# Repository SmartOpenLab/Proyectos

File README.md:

# Proyectos
Project's Repository of [Smart Open Lab](http://www.smartopenlab.com)

- Insoladora - Two faces PCB insolator device using UV light
- IoT_WeightMeasure - Weight measure device based on ESP8266
- Cerradura Biométrica - IoT door lock device based on fingerprints
- ESP rfid keypad access - Clone of [esp-rfid](https://github.com/esprfid/esp-rfid) 
- esp_rfid_SOL_V1 - IoT door lock device based on ESP8266 with RFID reader and keyboard. With custom PCB with MOSFET instead of relay.
- OpenSoundMeter - IoT sound preassure meter device.

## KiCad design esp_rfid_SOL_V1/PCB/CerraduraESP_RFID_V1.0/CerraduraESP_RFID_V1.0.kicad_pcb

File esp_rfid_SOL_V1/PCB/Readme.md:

Kicad files for the schematic and PCB.

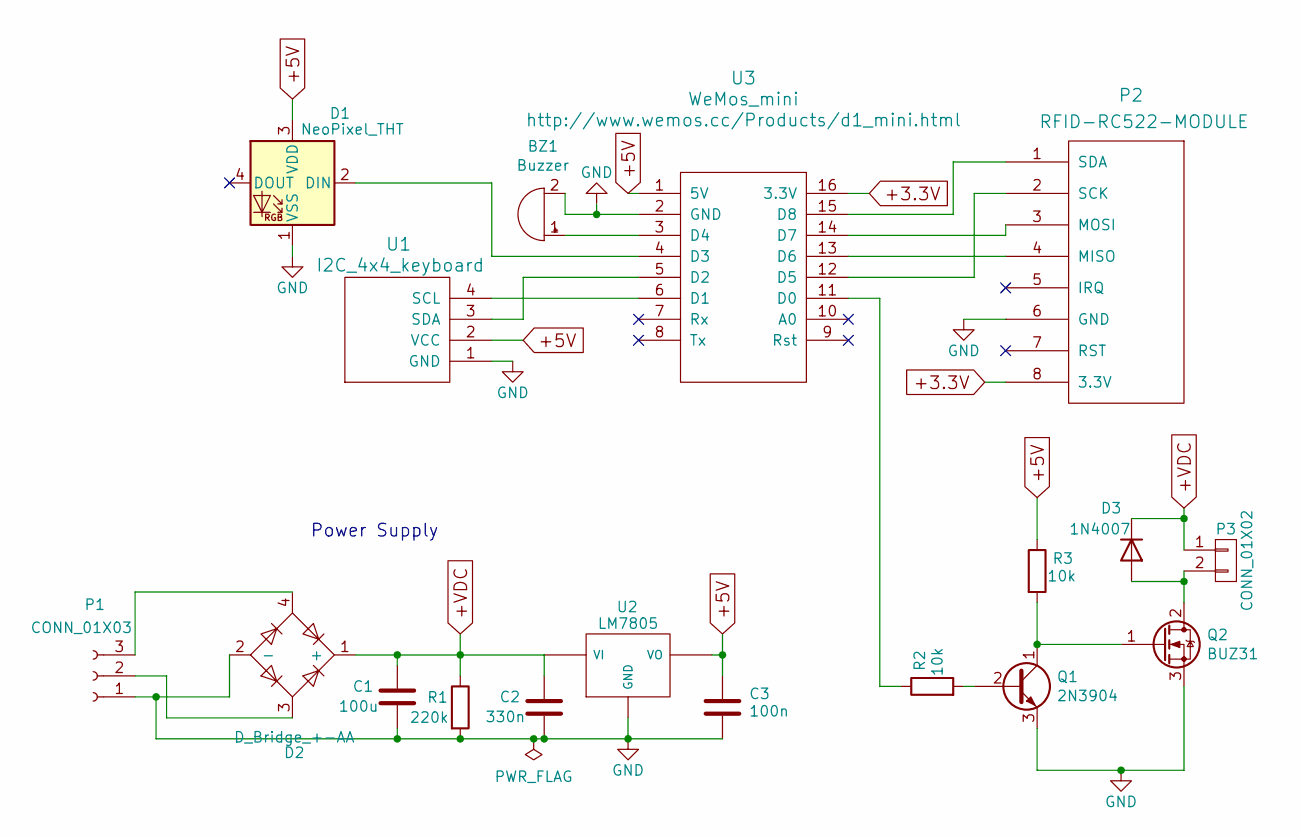
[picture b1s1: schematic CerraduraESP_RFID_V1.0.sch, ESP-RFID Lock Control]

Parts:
BZ1: Buzzer; Buzzer_12x9.5RM7.6
C1: 100u; CP_Radial_D10.0mm_P3.80mm
C2: 330n; C_Disc_D5.0mm_W2.5mm_P2.50mm
C3: 100n; C_Rect_L7.0mm_W2.5mm_P5.00mm
D1: NeoPixel_THT; Socket_Strip_Straight_1x03_Pitch2.54mm
D2: D_Bridge_+-AA; Diode_Bridge_Round_D8.9mm
D3: 1N4007; D_DO-41_SOD81_P7.62mm_Horizontal
P1: CONN_01X03; TerminalBlock_bornier-3_P5.08mm
P2: RFID-RC522-MODULE; Socket_Strip_Straight_1x08_Pitch2.54mm
P3: CONN_01X02; TerminalBlock_bornier-2_P5.08mm
Q1: 2N3904; TO-92_Inline_Wide
Q2: BUZ31; TO-220-3_Vertical
R1: 220k; R_Axial_DIN0207_L6.3mm_D2.5mm_P7.62mm_Horizontal
R2, R3: 10k; R_Axial_DIN0207_L6.3mm_D2.5mm_P7.62mm_Horizontal
U1: I2C_4x4_keyboard; Socket_Strip_Straight_1x04_Pitch2.54mm
U2: LM7805; TO-220-3_Vertical
U3: WeMos_mini; wemos-d1-mini-with-pin-header-and-connector

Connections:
+3.3V: P2.8 (3.3V), U3.16 (3.3V)
+5V: C3.1, D1.3 (VDD), R3.1, U1.2 (VCC), U2.3 (VO), U3.1 (5V)
+VDC: C1.1, C2.1, D2.1 (+), D3.1 (K), P3.1, R1.1, U2.1 (VI)
GND: BZ1.2 (+), C1.2, C2.2, C3.2, D1.1 (VSS), D2.2 (-), P1.1, P2.6 (GND), Q1.3 (E), Q2.3 (S), R1.2, U1.1 (GND), U2.2 (GND), U3.2 (GND)
unnamed: BZ1.1 (-), U3.3 (D4)
unnamed: D1.2 (DIN), U3.4 (D3)
unnamed: D2.3, P1.2
unnamed: D2.4, P1.3
unnamed: D3.2 (A), P3.2, Q2.2 (D)
unnamed: P2.1 (SDA), U3.15 (D8)
unnamed: P2.2 (SCK), U3.12 (D5)
unnamed: P2.3 (MOSI), U3.14 (D7)
unnamed: P2.4 (MISO), U3.13 (D6)
unnamed: Q1.1 (C), Q2.1 (G), R3.2
unnamed: Q1.2 (B), R2.2
unnamed: R2.1, U3.11 (D0)
unnamed: U1.3 (SDA), U3.5 (D2)
unnamed: U1.4 (SCL), U3.6 (D1)

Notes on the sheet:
Power Supply

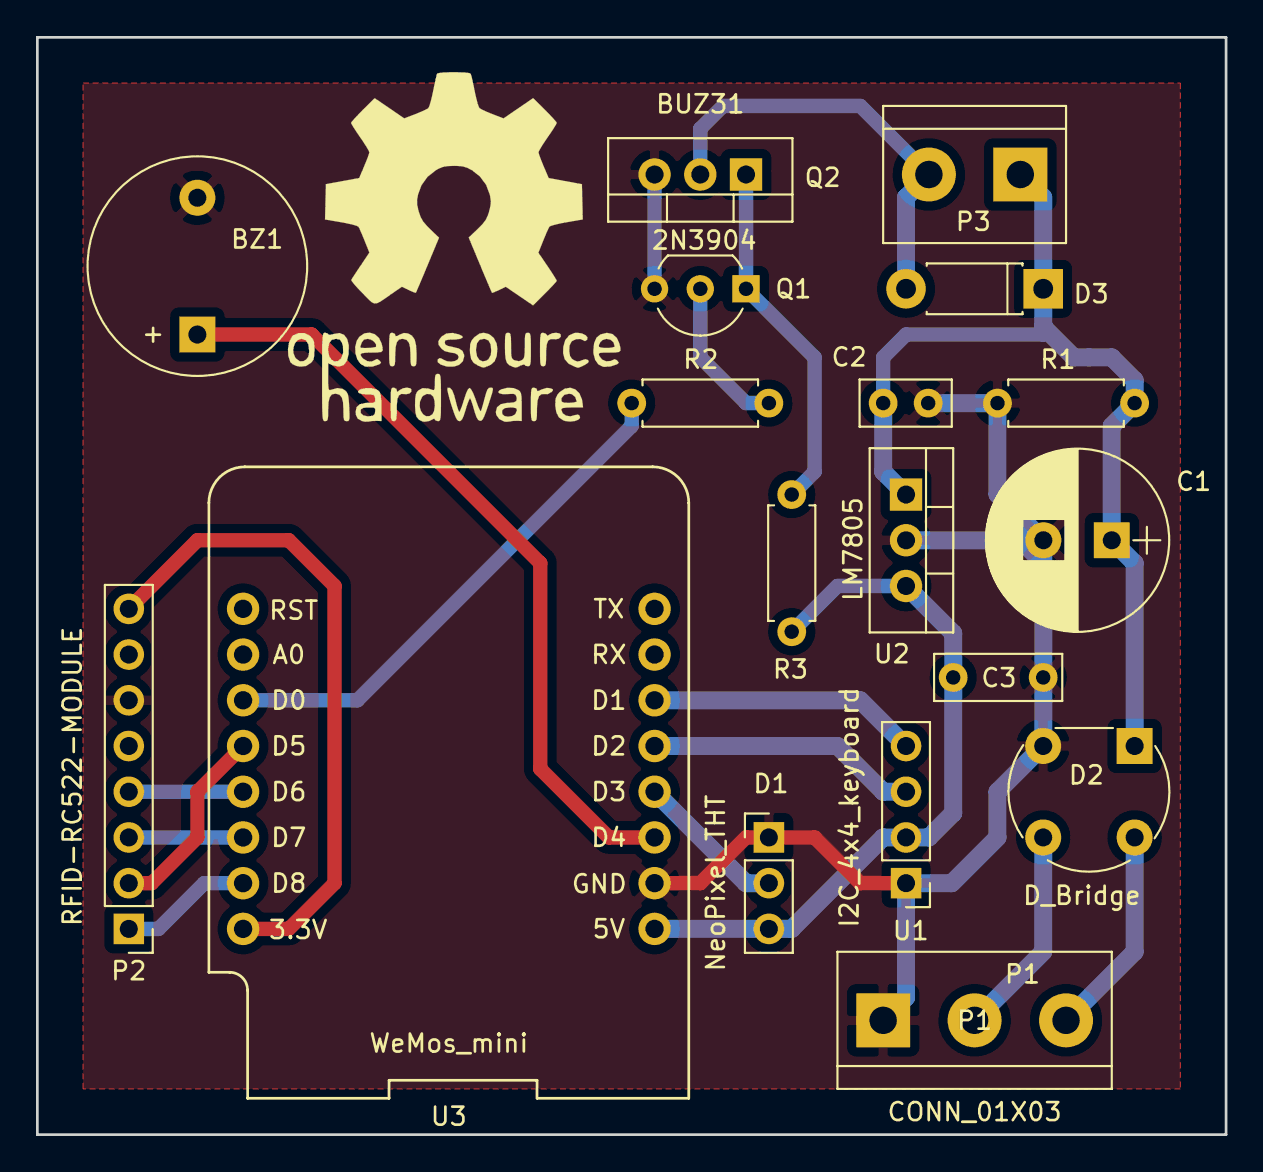
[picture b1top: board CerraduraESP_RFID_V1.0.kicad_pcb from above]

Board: 2 copper layers, 66.0 x 61.0 mm, 18 parts (0 on the bottom side), 18 nets.

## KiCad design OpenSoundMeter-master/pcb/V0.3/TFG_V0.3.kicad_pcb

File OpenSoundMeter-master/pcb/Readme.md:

# Electronic Design

We developed a PCB for preamplification, filtering and integration of the analog input signal.

### Prerequisites

Kicad 4.0 or later.

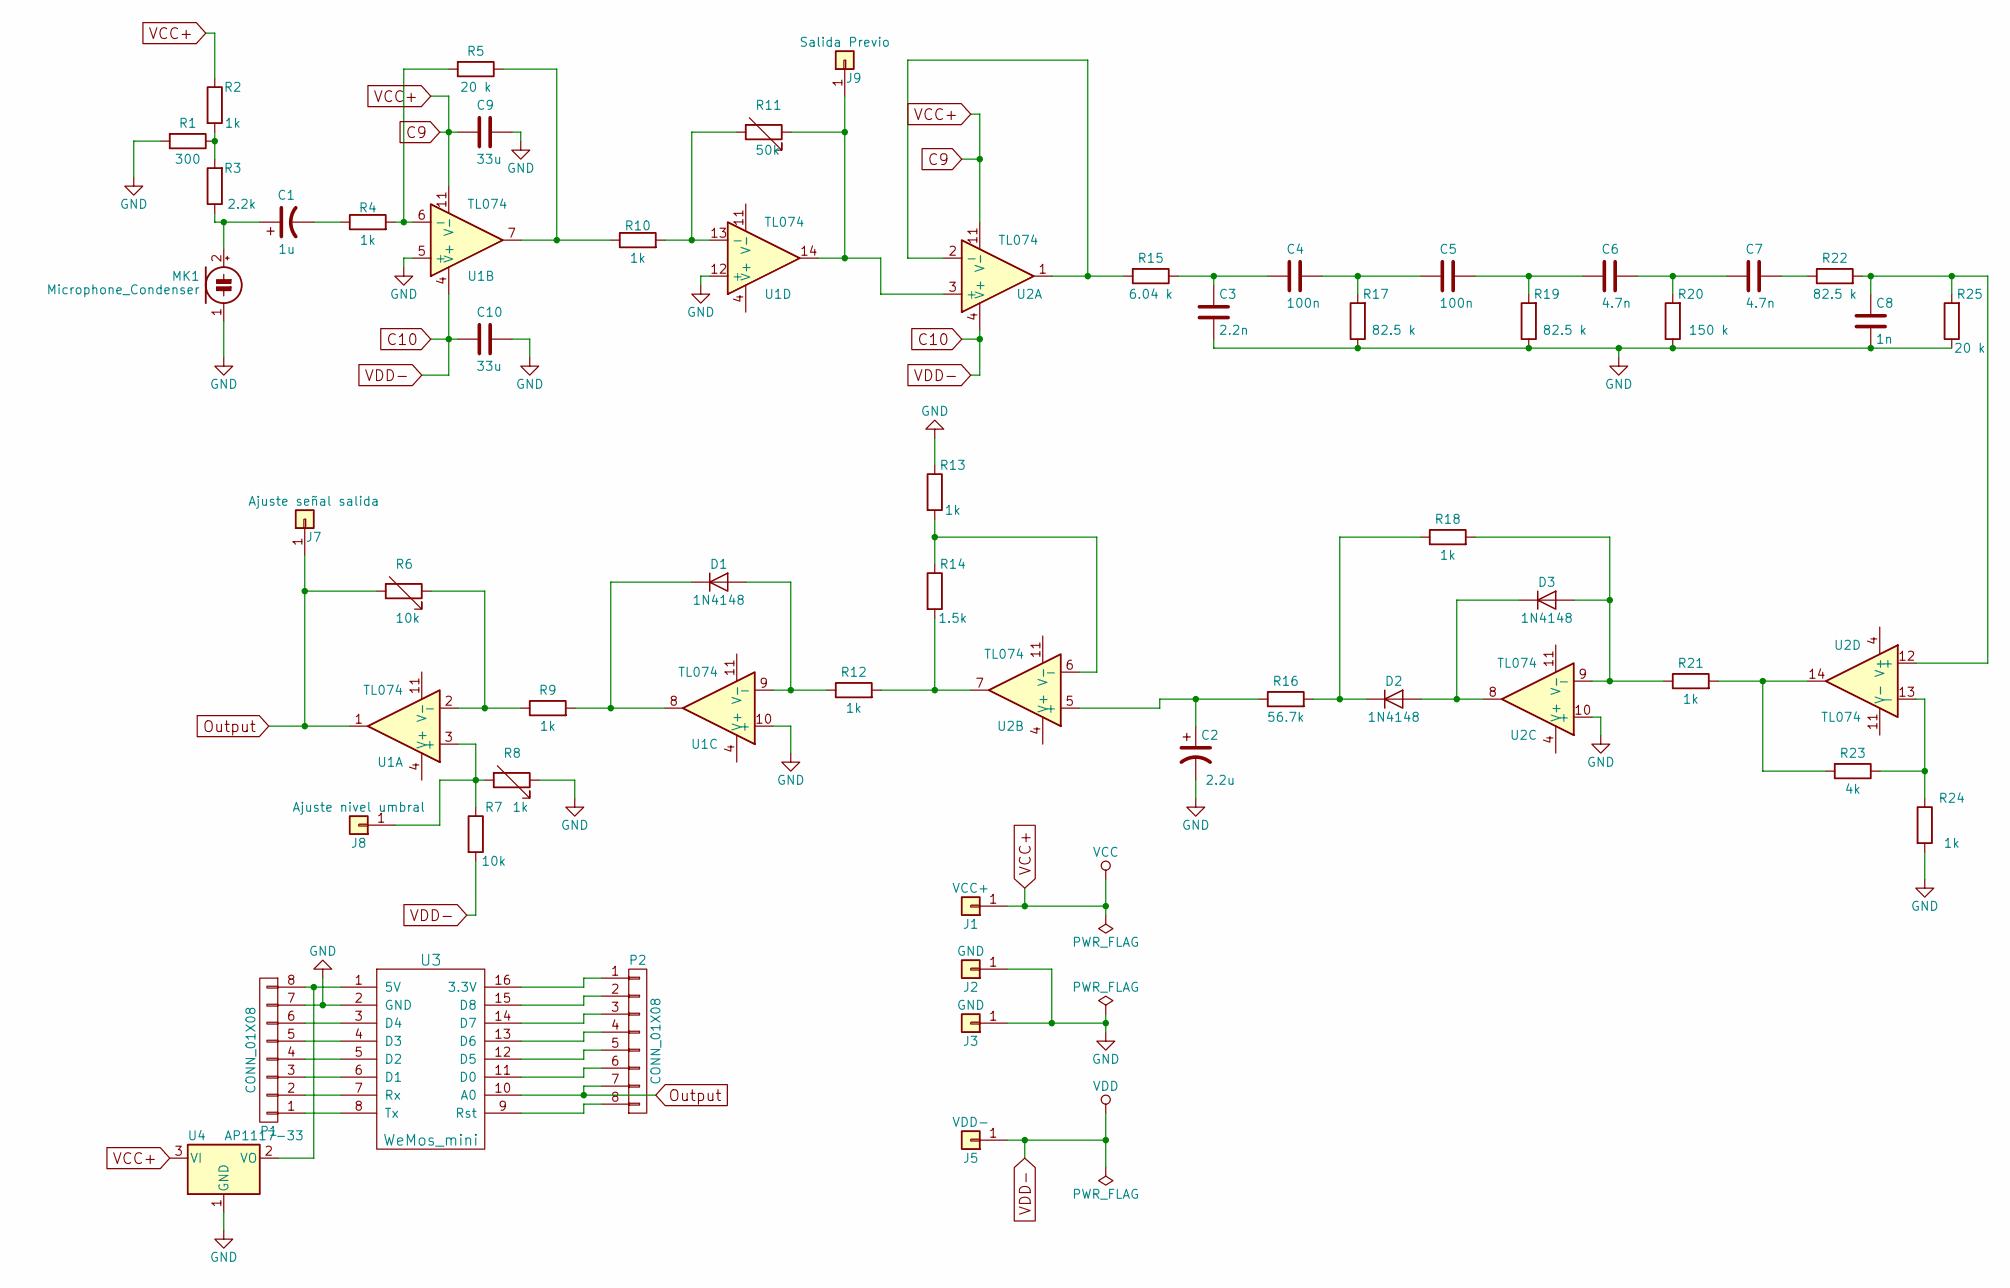
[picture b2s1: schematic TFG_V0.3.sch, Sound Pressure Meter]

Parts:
C1: 1u; C_Axial_L3.8mm_D2.6mm_P10.00mm_Horizontal
C2: 2.2u; C_Axial_L3.8mm_D2.6mm_P10.00mm_Horizontal
C3: 2.2n; C_Disc_D4.3mm_W1.9mm_P5.00mm
C4, C5: 100n; C_Rect_L7.0mm_W2.0mm_P5.00mm
C6, C7: 4.7n; C_Disc_D4.3mm_W1.9mm_P5.00mm
C8: 1n; C_Disc_D4.3mm_W1.9mm_P5.00mm
C9, C10: 33u; C_Axial_L3.8mm_D2.6mm_P10.00mm_Horizontal
D1, D2, D3: 1N4148; D_T-1_P5.08mm_Horizontal
J1: VCC+; Pin_Header_Angled_1x01_Pitch1.27mm
J2, J3: GND; Pin_Header_Angled_1x01_Pitch1.27mm
J5: VDD-; Pin_Header_Angled_1x01_Pitch1.27mm
J7: Ajuste señal salida; Pin_Header_Angled_1x01_Pitch1.27mm
J8: Ajuste nivel umbral; Pin_Header_Angled_1x01_Pitch1.27mm
J9: Salida Previo; Pin_Header_Angled_1x01_Pitch1.27mm
MK1: Microphone_Condenser; WireConnection_0.80mmDrill
P1, P2: CONN_01X08; Pin_Header_Straight_1x08_Pitch1.00mm
R1: 300; R_Axial_DIN0204_L3.6mm_D1.6mm_P7.62mm_Horizontal
R2, R4, R9, R10, R12, R13, R18, R21, R24: 1k; R_Axial_DIN0204_L3.6mm_D1.6mm_P7.62mm_Horizontal
R3: 2.2k; R_Axial_DIN0204_L3.6mm_D1.6mm_P7.62mm_Horizontal
R5, R25: 20 k; R_Axial_DIN0204_L3.6mm_D1.6mm_P7.62mm_Horizontal
R6: 10k; Potentiometer_Trimmer_Bourns_3296Y
R7: 10k; R_Axial_DIN0204_L3.6mm_D1.6mm_P7.62mm_Horizontal
R8: 1k; Potentiometer_Trimmer_Bourns_3296Y
R11: 50k; Potentiometer_Trimmer_Bourns_3296Y
R14: 1.5k; R_Axial_DIN0204_L3.6mm_D1.6mm_P7.62mm_Horizontal
R15: 6.04 k; R_Axial_DIN0204_L3.6mm_D1.6mm_P7.62mm_Horizontal
R16: 56.7k; R_Axial_DIN0204_L3.6mm_D1.6mm_P7.62mm_Horizontal
R17, R19, R22: 82.5 k; R_Axial_DIN0204_L3.6mm_D1.6mm_P7.62mm_Horizontal
R20: 150 k; R_Axial_DIN0204_L3.6mm_D1.6mm_P7.62mm_Horizontal
R23: 4k; R_Axial_DIN0204_L3.6mm_D1.6mm_P7.62mm_Horizontal
U1, U2: TL074; DIP-14_W7.62mm
U3: WeMos_mini; D1_mini_board
U4: AP1117-33; TO-220-3_Vertical

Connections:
C9: C9.2, J1.1, R2.1, U1.11 (V-), U2.11 (V-), U4.3 (VI)
C10: C10.2, J5.1, R7.2, U1.4 (V+), U2.4 (V+)
GND: C2.2, C3.2, C8.2, C9.1, C10.1, J2.1, J3.1, MK1.1 (-), P1.7, R1.2, R8.1, R13.1, R17.1, R19.1, R20.1, R24.2, R25.1, U1.5 (+), U1.10 (+), U1.12 (+), U2.10 (+), U3.2 (GND), U4.1 (GND)
unnamed: C1.1, MK1.2 (+), R3.1
unnamed: C1.2, R4.1
unnamed: C2.1, R16.1, U2.5 (+)
unnamed: C3.1, C4.2, R15.1
unnamed: C4.1, C5.2, R17.2
unnamed: C5.1, C6.2, R19.2
unnamed: C6.1, C7.2, R20.2
unnamed: C7.1, R22.1
unnamed: C8.1, R22.2, R25.2, U2.12 (+)
unnamed: D1.1 (K), R9.2, U1.8
unnamed: D1.2 (A), R12.1, U1.9 (-)
unnamed: D2.1 (K), R16.2, R18.1
unnamed: D2.2 (A), D3.1 (K), U2.8
unnamed: D3.2 (A), R18.2, R21.1, U2.9 (-)
unnamed: J8.1, R7.1, R8.2, U1.3 (+)
unnamed: J9.1, R11.1, U1.14, U2.3 (+)
unnamed: P1.1, U3.8 (Tx)
unnamed: P1.2, U3.7 (Rx)
unnamed: P1.3, U3.6 (D1)
unnamed: P1.4, U3.5 (D2)
unnamed: P1.5, U3.4 (D3)
unnamed: P1.6, U3.3 (D4)
unnamed: P1.8, U3.1 (5V), U4.2 (VO)
unnamed: P2.1, U3.16 (3.3V)
unnamed: P2.2, U3.15 (D8)
unnamed: P2.3, U3.14 (D7)
unnamed: P2.4, U3.13 (D6)
unnamed: P2.5, U3.12 (D5)
unnamed: P2.6, U3.11 (D0)
unnamed: P2.8, U3.9 (Rst)
unnamed: R1.1, R2.2, R3.2
unnamed: R4.2, R5.2, U1.6 (-)
unnamed: R6.1, R9.1, U1.2 (-)
unnamed: R5.1, R10.1, U1.7
unnamed: R10.2, R11.2, U1.13 (-)
unnamed: R12.2, R14.2, U2.7
unnamed: R13.2, R14.1, U2.6 (-)
unnamed: R15.2, U2.1, U2.2 (-)
unnamed: R21.2, R23.2, U2.14
unnamed: R23.1, R24.1, U2.13 (-)
Output: J7.1, P2.7, R6.2, U1.1, U3.10 (A0)

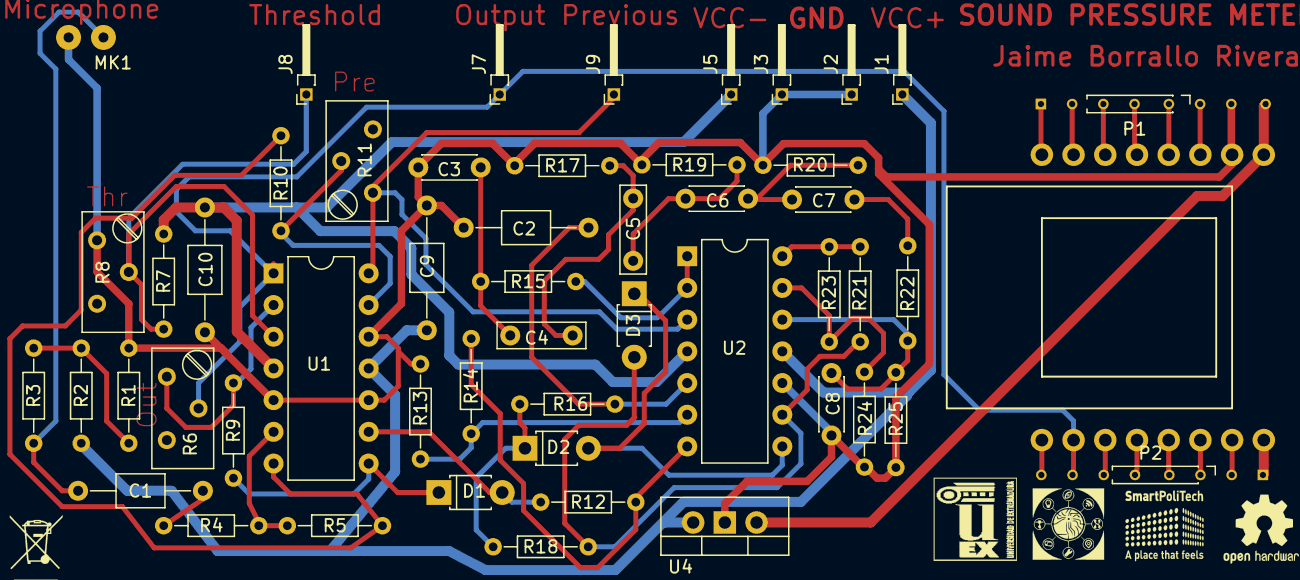
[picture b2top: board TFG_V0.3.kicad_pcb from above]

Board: 2 copper layers, 52 parts (1 on the bottom side), 44 nets.

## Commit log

2017-04-10 Añadido repositorio ejemploGit
2017-11-28 Añadido proyecto insoladora by @David867.
2017-11-28 Añadido el proyecto IoT_Balanza by @AGordiGuerrero.
2018-04-10 Añadido proyecto Cerradura Biométrica by @joriks
    Repositorio original: https://github.com/Joriks/Biometric-lock
2018-04-10 Actualizado readme con los proyectos
2019-01-11 Added a fork from esp-rfid v1.0.0
2019-01-11 Added password on website and save process for access
2019-01-20 Added empty value to default on new user
2019-01-27 Removed update by esp-rfid repository
2019-01-27 Removed neo bypass of admin settings
2019-10-21 Bump mixin-deep in /esp-rfid-keypad-access/tools/webfilesbuilder
    Bumps [mixin-deep](https://github.com/jonschlinkert/mixin-deep) from 1.3.1 to 1.3.2.
    - [Release notes](https://github.com/jonschlinkert/mixin-deep/releases)
    - [Commits](https://github.com/jonschlinkert/mixin-deep/compare/1.3.1...1.3.2)
2020-12-03 Added LICENSE BY-NC-SA
2020-12-03 Delete user from system
    Fully feature of manual deleting user from system
2020-12-03 Fixed minor bug on Unsubscribe print
    Deleted the view of the identifier and fixed unsubscribe help print
2020-12-03 Fixed bug end bracket of subscribe module
2020-12-03 Fixed bugs with Fingerprints uses
    Unsuscribe module did not erase finger_id correct.
    Check fingerprint module
    -Wait was skipped after the first pause
    -Infinite loop because of no check of state of fingerprint
    Check finger image infinite loop because of no check of state of fingerprint.
    Getter fingerprint changed delay to showLed module and added some Debug notes
2020-12-03 Added OLED Support
    Added OLED support with a 128x64px OLED and u8glib.
    Added draw module for print messages on OLED Screen
2020-12-03 Add new user to system
    Fully feature of adding new users to system
2020-12-03 Skeleton to using KeypadEvents
    Refactor of first code implementation (add and check fingerprints)
    added structure control defined on use cases
2020-12-03 Check Admin Fingerprints
    Checking fingerprints to control Admin recourses
2020-12-03 Added module to include new control fingerprint
    Control module with subscribe control fingerprint option implemented.
2020-12-03 Checking fingerprints, main case of biometric locker
    Check of any type of fingerprint returns fingerID if it exsits on system
2020-12-03 Added Compilation directive and Led Information
    Added Debug compilation directive to use it with screen prints and show information by Serial.
    Added a led module to show information with red, green and white leds for errors, pass and activity information
2020-12-03 Añadido fichero base de la cerradura biométrica
    Fichero con la base operativa de la cerradura biométrica
2020-12-03 Fixed bugs in subscribe & getting password
    Changed Keyboard input from Event Listener to Wait for key, locker method.
    Migrated code from Event Listener to main loop.
    Added to main loop getting password to store on system, because it fails because of nesting.
    Split getPassword module to check on one side an get on the other (getKeyPass module).
    Minor changes in variable names
2020-12-03 Obtain Fingerprint Model
    Obtain a fingerprint twice and genereate a model, with time chunk
2020-12-03 Added check password for subscribe module
    Added a checker password, with two comprobations to add new user into the system
2020-12-03 Added Check Access & changed relay & fingerprint pinout
    Added checkAccess module to check fingerprints and allow or deny access.
    Changed Relay pinout from Digital 10 to Analog 3
    Changed Fingerprint Sensor pinout from 11,12 to 10,11
2020-12-03 Changed all information messages from english to spanish
2020-12-03 Changed sensor pinout, deleted event keypad, deleted password nesting
    Changed sensor pinout from 11,12 to 10,11.
    Deleted Event listener from keypad, and added control to main loop.
    Deleted password nesting on getPassword to show information messages.
2020-12-03 Changed text of information messages
2020-12-03 Refactor of secundary modules
    Refactor and optimization of secundary modules
    Renamed modules with more understandable names
2020-12-03 Added Reset function by master keys
2020-12-03 Added Reset function by fingerprint
    Created factory Reset function to delete all and restore default settings
2020-12-03 Refactor of unsubscribe user
    optimization of unsubscribe user module using refactorized secundary modules
2020-12-03 Ccorreciones
2020-12-03 Added Unsubscribe control user function
2020-12-03 Correciones
2020-12-03 Added persistence feature
    Added persistence using EEPROM to save passwords and state of the system
2020-12-03 Revert "Added id info message on subscribe & info message on unsubscribe module"
    This reverts commit 1e845f3bf3ee7c0138c4196bffbc737122458188.
2020-12-03 Added id info message on subscribe & info message on unsubscribe module
    Added information message with id of the actual user adder to system.
    Added information message on unsubscribe module asking for a fingerprint.
2020-12-03 Added check of id data & Information on control checks
    Added check of integrity user & control id
    Added information error on check password of control module
2020-12-03 Changed condition to isdigit() & added compilation primitives
    Changed condition of check keycode to isdigit() from ascii decimal values
    Added compilation primitives to select LED, OLED or both modes
2020-12-03 Changed actuator opening time
    Changed to 100 ms to use dc and control status of actuator
2020-12-03 Adjust of all information messages printed on OLED
2020-12-03 Migrated Serial library uses to DEBUG MODE
2020-12-03 Fixed Display of user information over Serial and OLED
    Temporal fixed to display user id over OLED
2020-12-03 Merged from remote repo
2020-12-11 Bump ini in /esp-rfid-keypad-access/tools/webfilesbuilder
    Bumps [ini](https://github.com/isaacs/ini) from 1.3.5 to 1.3.7.
    - [Release notes](https://github.com/isaacs/ini/releases)
    - [Commits](https://github.com/isaacs/ini/compare/v1.3.5...v1.3.7)
2021-08-10 Bump path-parse in /esp-rfid-keypad-access/tools/webfilesbuilder
    Bumps [path-parse](https://github.com/jbgutierrez/path-parse) from 1.0.6 to 1.0.7.
    - [Release notes](https://github.com/jbgutierrez/path-parse/releases)
    - [Commits](https://github.com/jbgutierrez/path-parse/commits/v1.0.7)
    ---
    updated-dependencies:
    - dependency-name: path-parse
2021-12-08 Create ESP-RFID-KEYBOARD_SOL_V1
2022-11-01 Bump minimatch and gulp in /esp-rfid-keypad-access/tools/webfilesbuilder
    Bumps [minimatch](https://github.com/isaacs/minimatch) to 3.1.2 and updates ancestor dependency [gulp](https://github.com/gulpjs/gulp). These dependencies need to be updated together.
    Updates `minimatch` from 0.2.14 to 3.1.2
    - [Release notes](https://github.com/isaacs/minimatch/releases)
    - [Commits](https://github.com/isaacs/minimatch/compare/v0.2.14...v3.1.2)
    Updates `gulp` from 3.9.1 to 4.0.2
    - [Release notes](https://github.com/gulpjs/gulp/releases)
2022-12-02 Bump decode-uri-component
    Bumps [decode-uri-component](https://github.com/SamVerschueren/decode-uri-component) from 0.2.0 to 0.2.2.
    - [Release notes](https://github.com/SamVerschueren/decode-uri-component/releases)
    - [Commits](https://github.com/SamVerschueren/decode-uri-component/compare/v0.2.0...v0.2.2)
    ---
    updated-dependencies:
    - dependency-name: decode-uri-component
2023-02-28 Bump minimist and mkdirp
    Bumps [minimist](https://github.com/minimistjs/minimist) and [mkdirp](https://github.com/isaacs/node-mkdirp). These dependencies needed to be updated together.
    Updates `minimist` from 1.2.0 to 1.2.8
    - [Release notes](https://github.com/minimistjs/minimist/releases)
    - [Changelog](https://github.com/minimistjs/minimist/blob/main/CHANGELOG.md)
    - [Commits](https://github.com/minimistjs/minimist/compare/v1.2.0...v1.2.8)
    Updates `mkdirp` from 0.5.1 to 0.5.6
2023-04-18 Bump lodash and gulp in /esp-rfid-keypad-access/tools/webfilesbuilder
    Bumps [lodash](https://github.com/lodash/lodash) to 4.17.21 and updates ancestor dependency [gulp](https://github.com/gulpjs/gulp). These dependencies need to be updated together.
    Updates `lodash` from 4.17.11 to 4.17.21
    - [Release notes](https://github.com/lodash/lodash/releases)
    - [Commits](https://github.com/lodash/lodash/compare/4.17.11...4.17.21)
    Updates `gulp` from 3.9.1 to 4.0.2
    - [Release notes](https://github.com/gulpjs/gulp/releases)
